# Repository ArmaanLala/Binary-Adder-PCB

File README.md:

# Binary-Adder-PCB
## Summary
This circuit uses the 4-bit adder IC.

## Schematic and Board layout

The figure above shows a schematic of the Binary Adder circuit. 
Layout summary:
- The power jack on the opposing side and thus out of the way of the user. 

The figure above shows a board view implementing the above schematic. 

Layout summary:
- The power jack on the opposing side and thus out of the way of the user. 
- The user selects the input A and B on the side nearest to the user.
- The 4008N in between input switches and out LEDs.
- The LEDs near the opp.

## Credits
This Eagle project is a personal collaboration project between Armaan Lala and Peter Chu.

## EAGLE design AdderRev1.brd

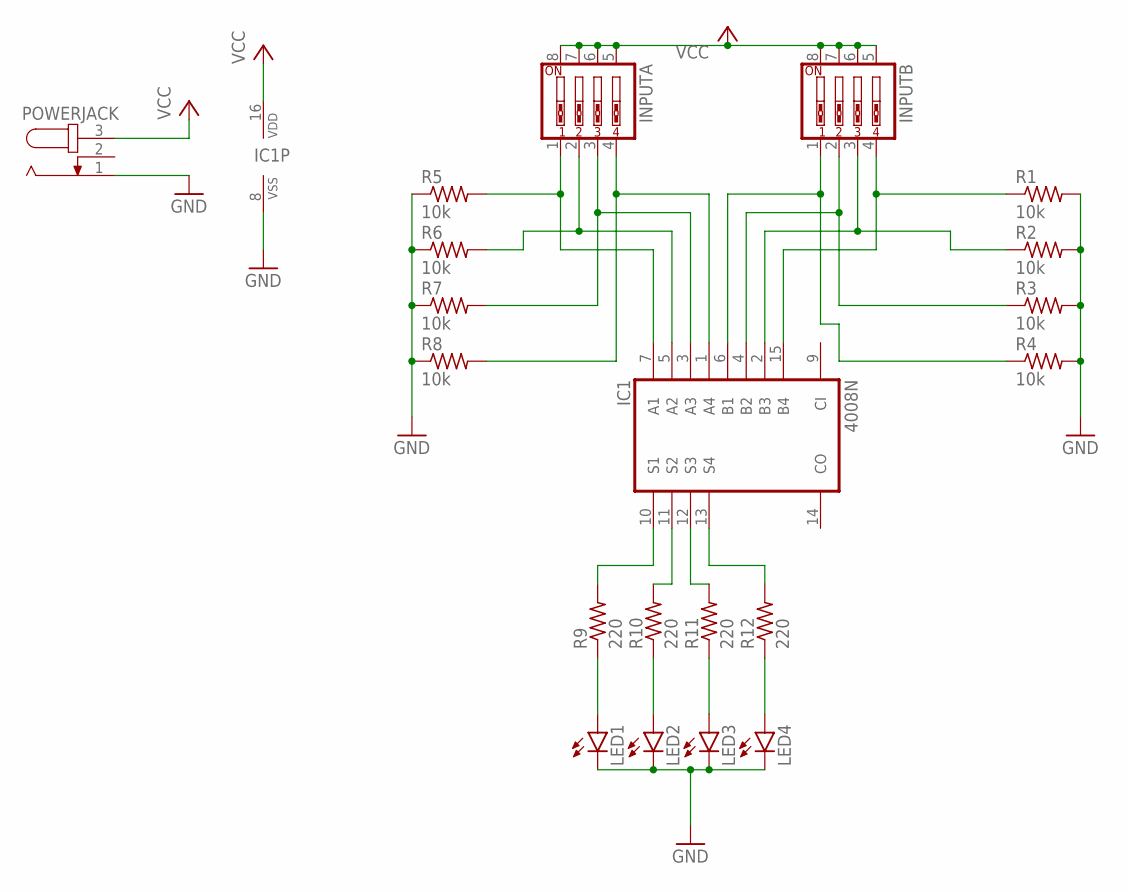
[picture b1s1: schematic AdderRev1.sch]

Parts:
IC1: 4008N; DIL16
INPUTA: SW_DIP-4; EDG-04
INPUTB: SW_DIP-4; EDG-04
LED1, LED2, LED3, LED4: LED5MM
POWERJACK: JACK-PLUG1; SPC4078
R1, R2, R3, R4, R5, R6, R7, R8: 10k; 0204/7
R9, R10, R11, R12: 220; 0204/7

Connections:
GND: IC1.8 (VSS), LED1.K (C), LED2.K (C), LED3.K (C), LED4.K (C), POWERJACK.1, R1.2, R2.2, R3.2, R4.2, R5.1, R6.1, R7.1, R8.1
unnamed: IC1.7 (A1), INPUTA.1, R5.2
unnamed: IC1.5 (A2), INPUTA.2, R6.2
unnamed: IC1.3 (A3), INPUTA.3, R7.2
unnamed: IC1.1 (A4), INPUTA.4, R8.2
unnamed: IC1.6 (B1), INPUTB.1, R4.1
unnamed: IC1.4 (B2), INPUTB.2, R3.1
unnamed: IC1.2 (B3), INPUTB.3, R2.1
unnamed: IC1.15 (B4), INPUTB.4, R1.1
unnamed: IC1.11 (S2), R10.2
unnamed: IC1.12 (S3), R11.2
unnamed: IC1.10 (S1), R9.2
unnamed: IC1.13 (S4), R12.2
unnamed: LED1.A, R9.1
unnamed: LED2.A, R10.1
unnamed: LED3.A, R11.1
unnamed: LED4.A, R12.1
VCC: IC1.16 (VDD), INPUTA.5, INPUTA.6, INPUTA.7, INPUTA.8, INPUTB.5, INPUTB.6, INPUTB.7, INPUTB.8, POWERJACK.3

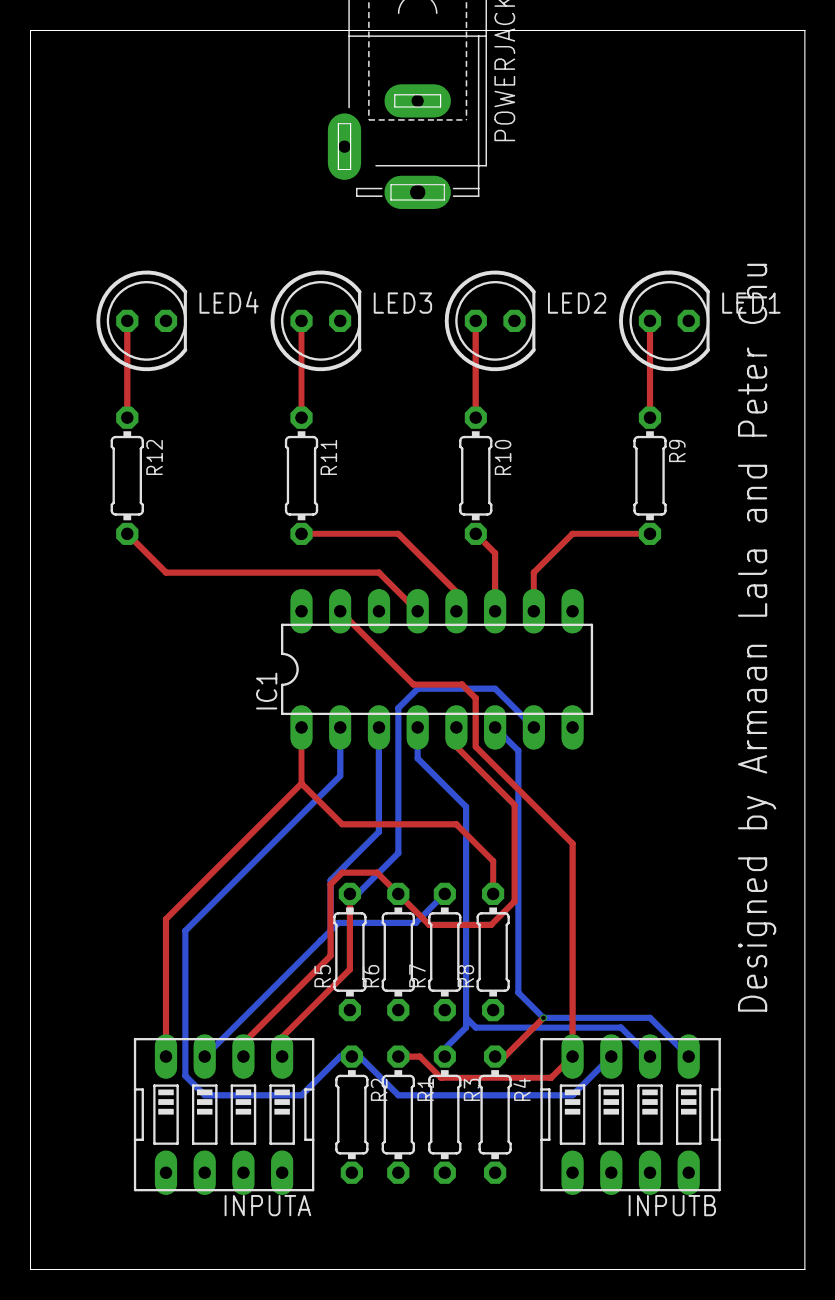
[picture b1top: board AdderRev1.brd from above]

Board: 2 copper layers, 50.8 x 81.3 mm, 20 parts (0 on the bottom side), 18 nets.

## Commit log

2020-12-10 Finished Designing PCB
2020-12-12 Added design frame and title block to sch file and added images to repository and readme
2020-12-13 Updated the image URLs in readme
2020-12-13 Added some documentation and updated to high resolution images
2021-01-09 Testing if mac can committ to remote
